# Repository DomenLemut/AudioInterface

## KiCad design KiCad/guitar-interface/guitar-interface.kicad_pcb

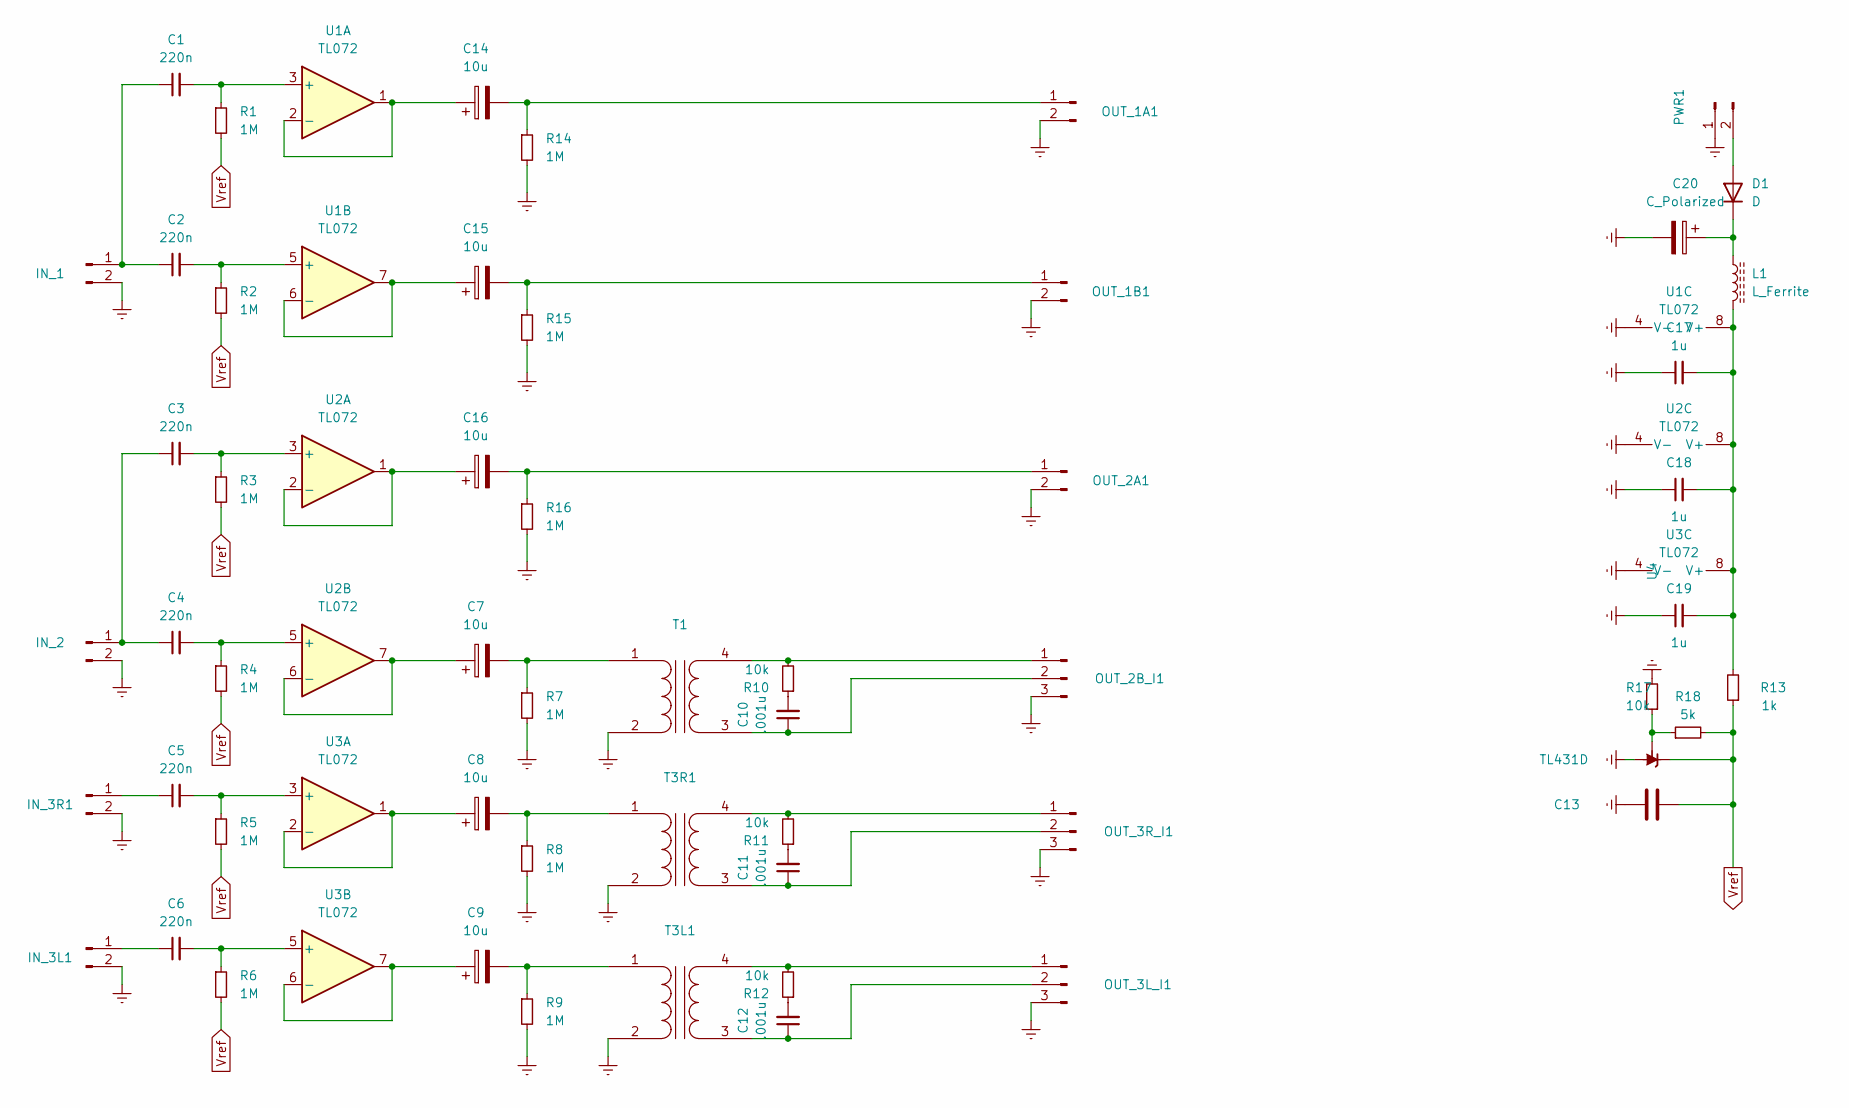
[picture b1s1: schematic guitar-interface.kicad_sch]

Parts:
C1, C2, C3, C4, C5, C6: 220n; C_0805_2012Metric_Pad1.18x1.45mm_HandSolder
C7, C8, C9, C14, C15, C16: 10u; CP_EIA-7343-30_AVX-N_Pad2.25x2.55mm_HandSolder
C10, C11, C12: .001u; C_0805_2012Metric_Pad1.18x1.45mm_HandSolder
C13: C; C_0805_2012Metric_Pad1.18x1.45mm_HandSolder
C17, C18, C19: 1u; C_0805_2012Metric_Pad1.18x1.45mm_HandSolder
C20: C_Polarized; CP_Elec_8x10
D1: D; D_0805_2012Metric_Pad1.15x1.40mm_HandSolder
IN_1, IN_2, IN_3L1, IN_3R1: Conn_01x02_Pin; SolderWire-0.5sqmm_1x02_P4.6mm_D0.9mm_OD2.1mm
L1: L_Ferrite; L_7.3x7.3_H3.5
OUT_1A1, OUT_1B1, OUT_2A1: Conn_01x02_Pin; SolderWire-0.5sqmm_1x02_P4.6mm_D0.9mm_OD2.1mm
OUT_2B_I1, OUT_3L_I1, OUT_3R_I1: Conn_01x03_Pin; SolderWire-0.5sqmm_1x03_P4.6mm_D0.9mm_OD2.1mm
PWR1: Conn_01x02_Pin; SolderWire-0.5sqmm_1x02_P4.6mm_D0.9mm_OD2.1mm
R1, R2, R3, R4, R5, R6, R7, R8, R9, R14, R15, R16: 1M; R_0805_2012Metric_Pad1.20x1.40mm_HandSolder
R10, R11, R12, R17: 10k; R_0805_2012Metric_Pad1.20x1.40mm_HandSolder
R13: 1k; R_0805_2012Metric_Pad1.20x1.40mm_HandSolder
R18: 5k; R_0805_2012Metric_Pad1.20x1.40mm_HandSolder
T1, T3L1, T3R1: Transformer_1P_1S; Tansformer 11
U1, U2, U3: TL072; D8_TEX_STM
U4: TL431D; SOIC-8_3.9x4.9mm_P1.27mm

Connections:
Earth: C13.1, C17.1, C18.1, C19.1, C20.2, IN_1.2, IN_2.2, IN_3L1.2, IN_3R1.2, OUT_1A1.2, OUT_1B1.2, OUT_2A1.2, OUT_2B_I1.3, OUT_3L_I1.3, OUT_3R_I1.3, PWR1.1, R7.2, R8.2, R9.2, R14.2, R15.2, R16.2, R17.2, T1.2 (AB), T3L1.2 (AB), T3R1.2 (AB), U1.4 (V-), U2.4 (V-), U3.4 (V-), U4.2 (A), U4.3 (A), U4.6 (A), U4.7 (A)
unnamed: C10.2, R10.1
unnamed: C11.2, R11.1
unnamed: C12.2, R12.1
unnamed: D1.2 (A), PWR1.2
unnamed: C20.1, D1.1 (K), L1.1
unnamed: C1.1, C2.1, IN_1.1
unnamed: C3.1, C4.1, IN_2.1
unnamed: C6.1, IN_3L1.1
unnamed: C5.1, IN_3R1.1
unnamed: C14.2, OUT_1A1.1, R14.1
unnamed: C15.2, OUT_1B1.1, R15.1
unnamed: C16.2, OUT_2A1.1, R16.1
unnamed: OUT_2B_I1.1, R10.2, T1.4 (SB)
unnamed: C10.1, OUT_2B_I1.2, T1.3 (SA)
unnamed: OUT_3L_I1.1, R12.2, T3L1.4 (SB)
unnamed: C12.1, OUT_3L_I1.2, T3L1.3 (SA)
unnamed: OUT_3R_I1.1, R11.2, T3R1.4 (SB)
unnamed: C11.1, OUT_3R_I1.2, T3R1.3 (SA)
unnamed: C7.2, R7.1, T1.1 (AA)
unnamed: C9.2, R9.1, T3L1.1 (AA)
unnamed: C8.2, R8.1, T3R1.1 (AA)
unnamed: C1.2, R1.1, U1.3 (+)
unnamed: C14.1, U1.1, U1.2 (-)
unnamed: C2.2, R2.1, U1.5 (+)
unnamed: C15.1, U1.6 (-), U1.7
unnamed: C17.2, C18.2, C19.2, L1.2, R13.2, U1.8 (V+), U2.8 (V+), U3.8 (V+)
unnamed: C3.2, R3.1, U2.3 (+)
unnamed: C16.1, U2.1, U2.2 (-)
unnamed: C4.2, R4.1, U2.5 (+)
unnamed: C7.1, U2.6 (-), U2.7
unnamed: C5.2, R5.1, U3.3 (+)
unnamed: C8.1, U3.1, U3.2 (-)
unnamed: C6.2, R6.1, U3.5 (+)
unnamed: C9.1, U3.6 (-), U3.7
unnamed: R17.1, R18.1, U4.8 (REF)
Vref: C13.2, R1.2, R2.2, R3.2, R4.2, R5.2, R6.2, R13.1, R18.2, U4.1 (K)

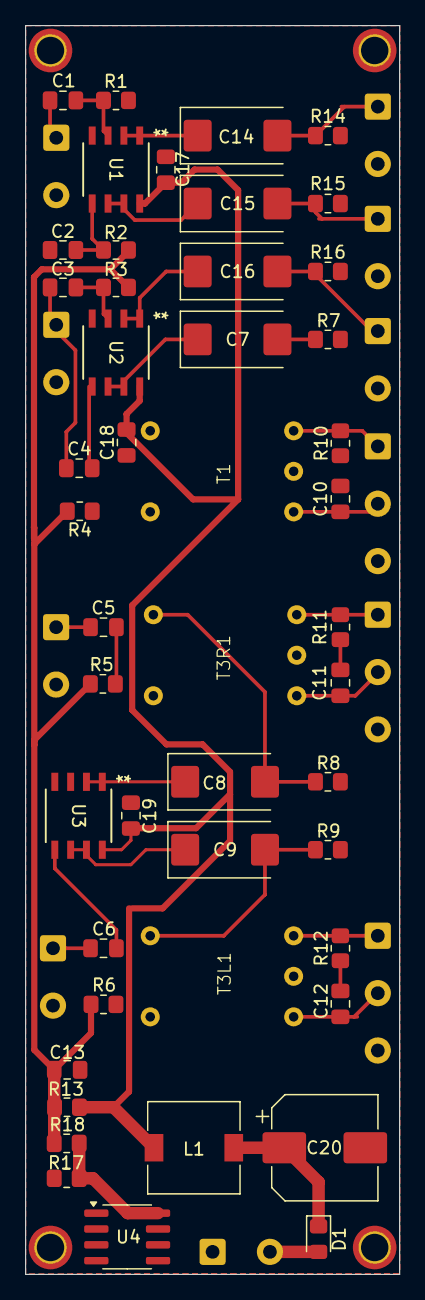
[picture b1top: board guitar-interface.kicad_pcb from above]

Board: 2 copper layers, 30.0 x 100.2 mm, 58 parts (0 on the bottom side), 37 nets.

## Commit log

2025-03-20 init
